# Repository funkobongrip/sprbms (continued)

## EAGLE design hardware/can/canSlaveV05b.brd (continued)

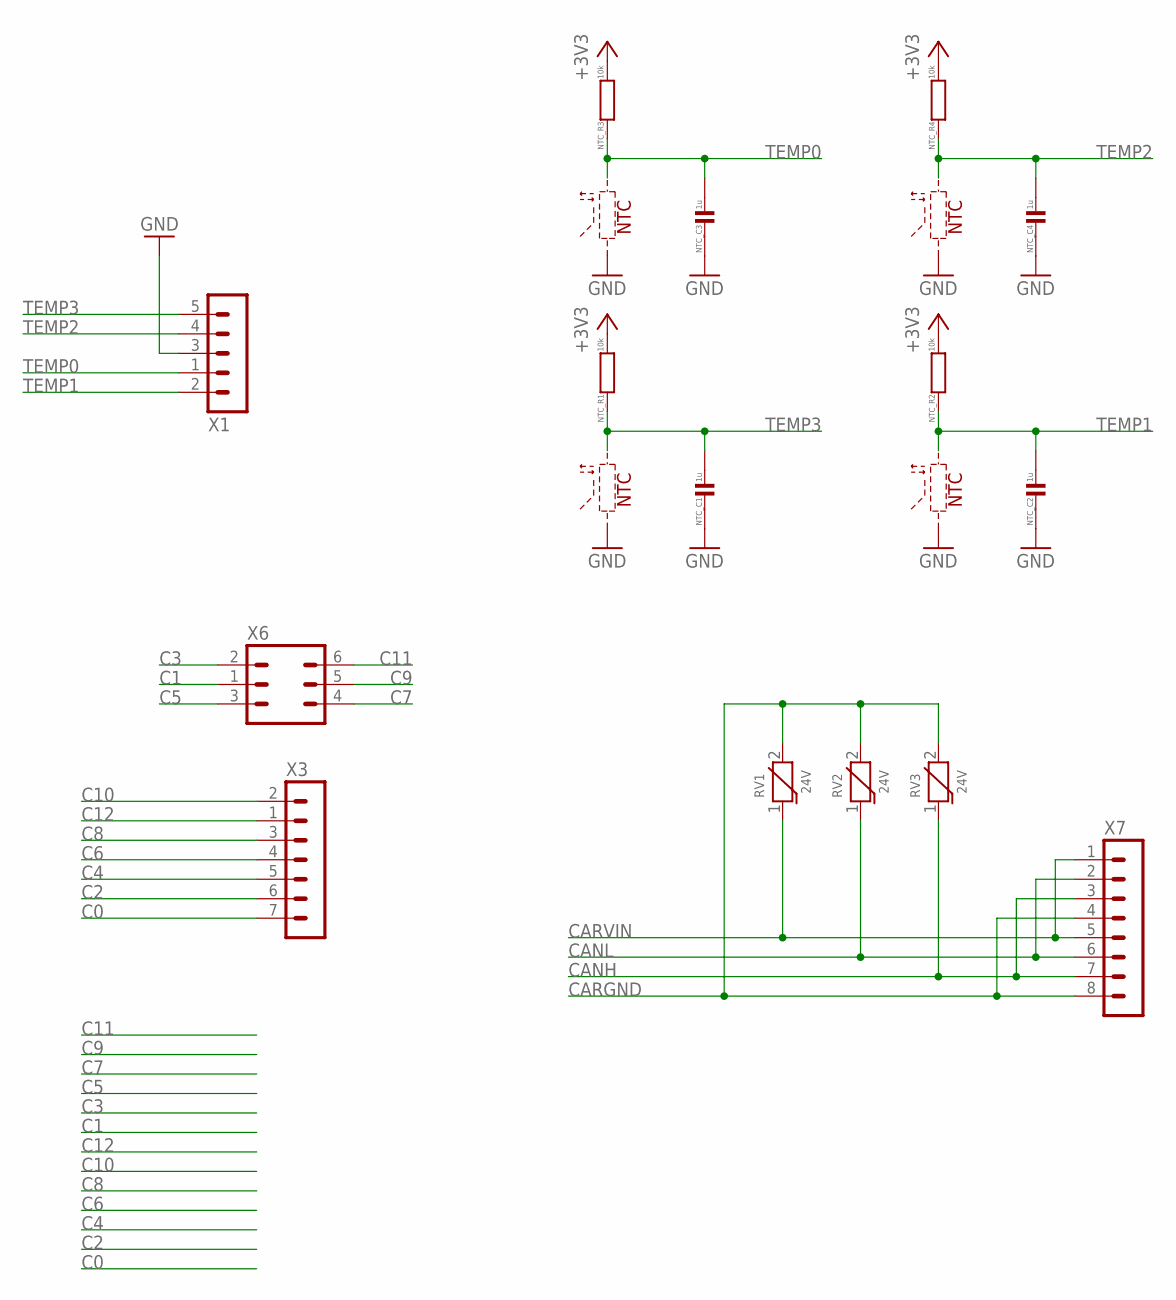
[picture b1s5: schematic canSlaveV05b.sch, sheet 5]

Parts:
NTC_C1, NTC_C2, NTC_C3, NTC_C4: 1u; C0402
NTC_R1, NTC_R2, NTC_R3, NTC_R4: 10k; R0402
RV1: 24V; R0805
RV2, RV3: 24V; R0603
X1: HEADER_POS5_43650-0509; 43650-0509
X3: HEADER_POS7_43650-0709; 43650-0709
X6: HEADER_POS6_43650-0609; 43650-0609
X7: HEADER_POS8_43045-0800; 43045-0800

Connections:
+3V3: NTC_R1.2, NTC_R2.2, NTC_R3.2, NTC_R4.2; also elsewhere on the board
C0: X3.7; also elsewhere on the board
C1: X6.1 (2); also elsewhere on the board
C2: X3.6; also elsewhere on the board
C3: X6.2 (1); also elsewhere on the board
C4: X3.5; also elsewhere on the board
C5: X6.3; also elsewhere on the board
C6: X3.4; also elsewhere on the board
C7: X6.4; also elsewhere on the board
C8: X3.3; also elsewhere on the board
C9: X6.5; also elsewhere on the board
C10: X3.2 (1); also elsewhere on the board
C11: X6.6; also elsewhere on the board
C12: X3.1 (2); also elsewhere on the board
CANH: RV3.1, X7.3, X7.7; also elsewhere on the board
CANL: RV2.1, X7.2, X7.6; also elsewhere on the board
CARGND: RV1.2, RV2.2, RV3.2, X7.4, X7.8; also elsewhere on the board
CARVIN: RV1.1, X7.1, X7.5; also elsewhere on the board
GND: NTC_C1.2, NTC_C2.2, NTC_C3.2, NTC_C4.2, X1.3; also elsewhere on the board
TEMP0: NTC_C3.1, NTC_R3.1, X1.1 (2); also elsewhere on the board
TEMP1: NTC_C2.1, NTC_R2.1, X1.2 (1); also elsewhere on the board
TEMP2: NTC_C4.1, NTC_R4.1, X1.4; also elsewhere on the board
TEMP3: NTC_C1.1, NTC_R1.1, X1.5; also elsewhere on the board

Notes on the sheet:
NTC

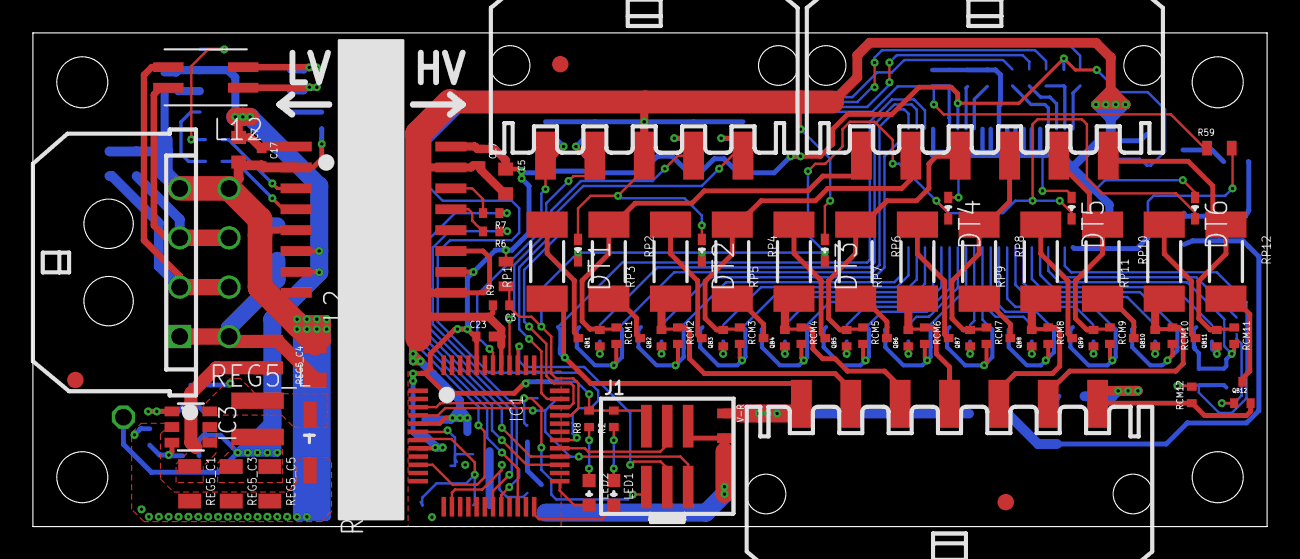
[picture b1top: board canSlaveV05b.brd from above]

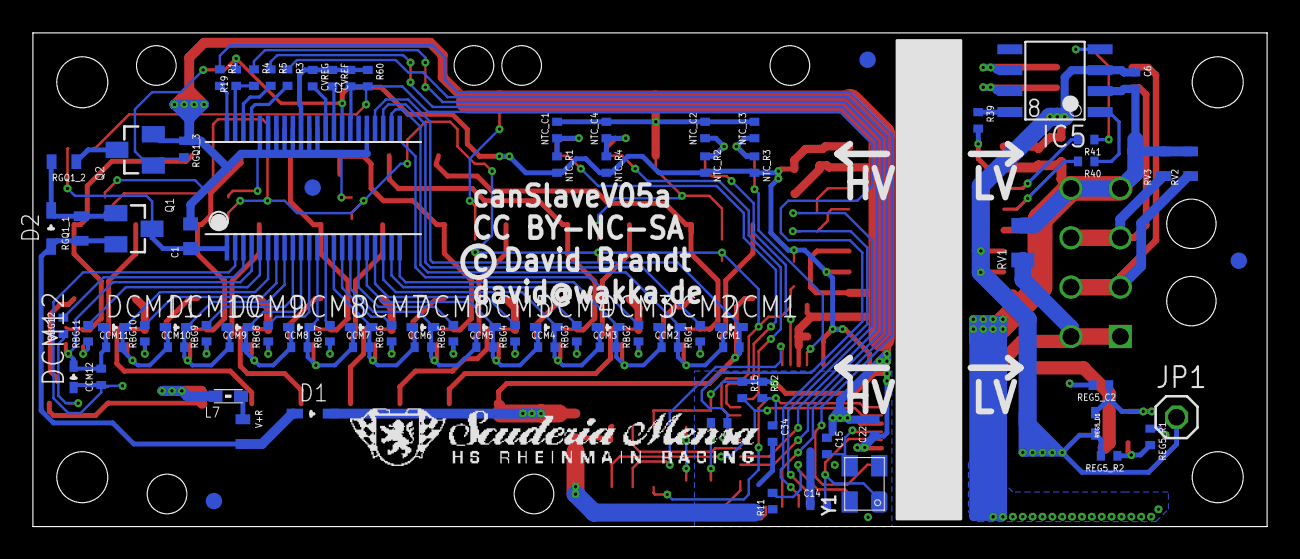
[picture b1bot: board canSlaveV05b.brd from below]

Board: 2 copper layers, 75.0 x 30.0 mm, 167 parts (90 on the bottom side), 115 nets.

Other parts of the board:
U$3: SMLOGOS_BSILK

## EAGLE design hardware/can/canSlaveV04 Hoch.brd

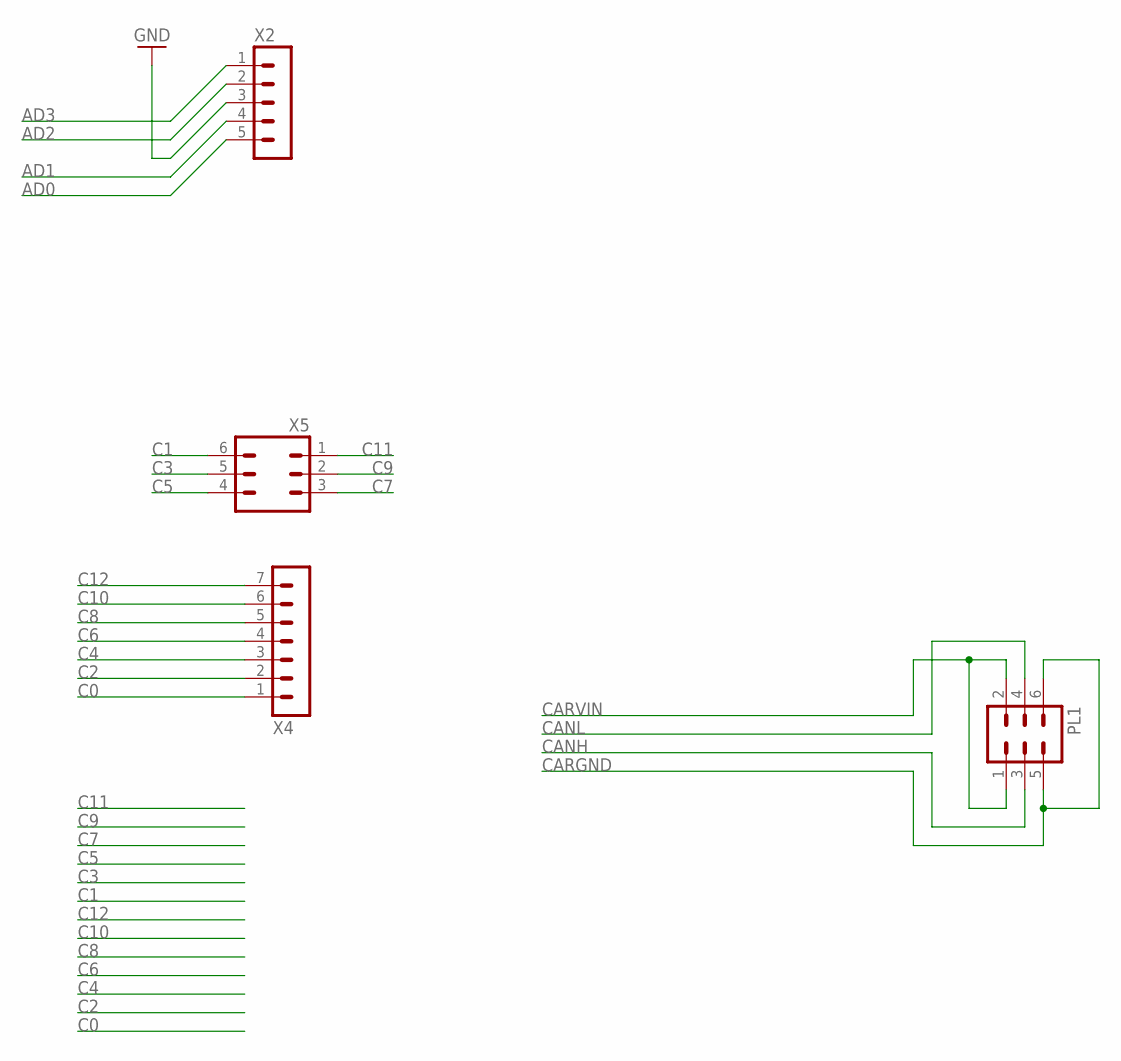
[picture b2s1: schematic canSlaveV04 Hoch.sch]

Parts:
PL1: 06V
X2: HEADER_POS5_43650-0515; 43650-0515
X4: HEADER_POS7_43650-0715; 43650-0715
X5: HEADER_POS6_43650-0615; 43650-0615

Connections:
AD0: X2.5
AD1: X2.4
AD2: X2.2
AD3: X2.1
C0: X4.1
C1: X5.6
C2: X4.2
C3: X5.5
C4: X4.3
C5: X5.4
C6: X4.4
C7: X5.3
C8: X4.5
C9: X5.2
C10: X4.6
C11: X5.1
C12: X4.7
CANH: PL1.3
CANL: PL1.4
CARGND: PL1.5, PL1.6
CARVIN: PL1.1, PL1.2
GND: X2.3

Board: 4 copper layers, 4 parts (0 on the bottom side), 2 nets, no tracks yet.

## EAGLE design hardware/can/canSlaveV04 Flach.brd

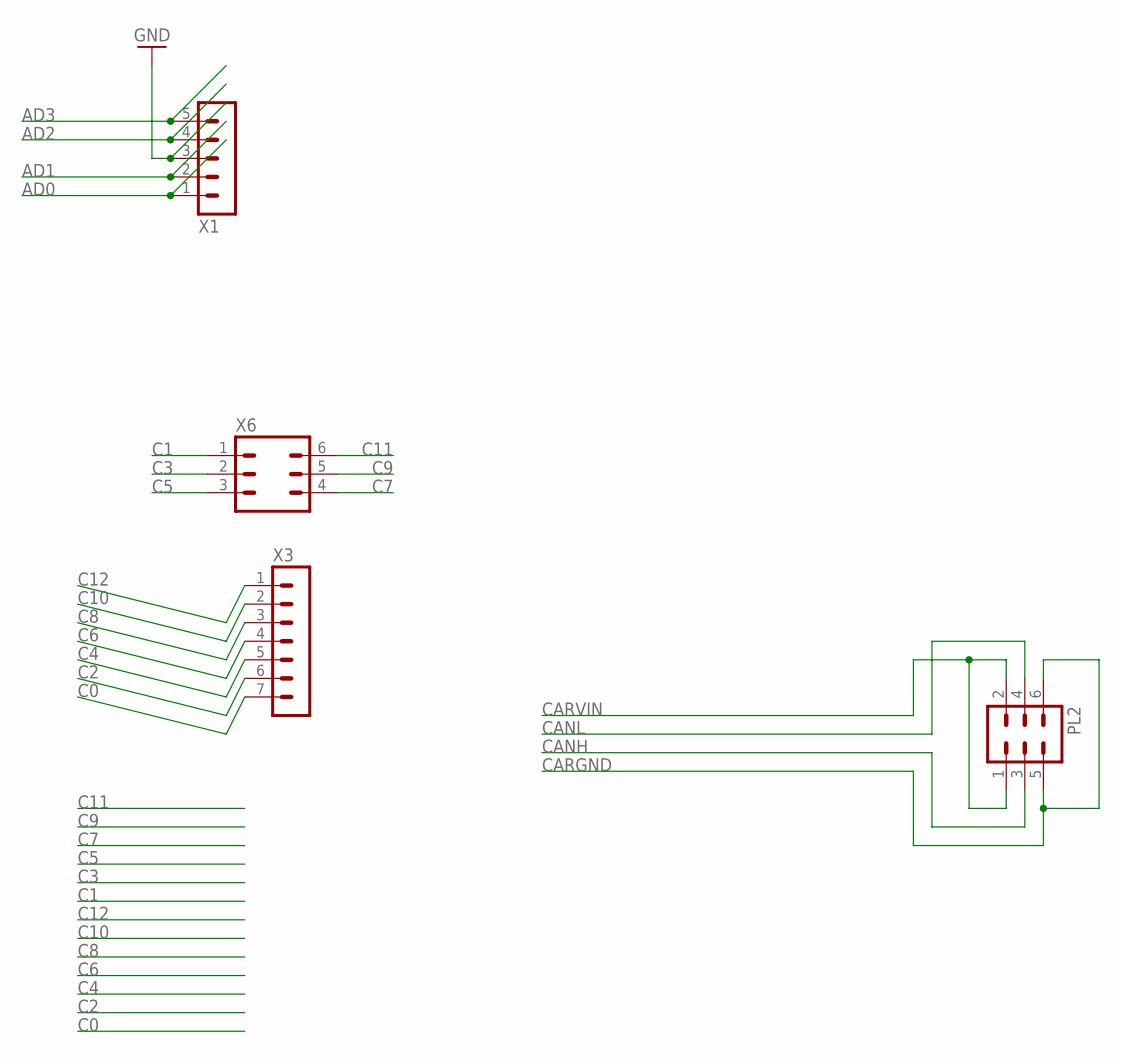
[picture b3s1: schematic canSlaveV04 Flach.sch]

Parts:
PL2: 06H
X1: HEADER_POS5_43650-0500; 43650-0500
X3: HEADER_POS7_43650-0700; 43650-0700
X6: HEADER_POS6_43650-0600; 43650-0600

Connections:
AD0: X1.1
AD1: X1.2
AD2: X1.4
AD3: X1.5
C0: X3.7
C1: X6.1
C2: X3.6
C3: X6.2
C4: X3.5
C5: X6.3
C6: X3.4
C7: X6.4
C8: X3.3
C9: X6.5
C10: X3.2
C11: X6.6
C12: X3.1
CANH: PL2.3
CANL: PL2.4
CARGND: PL2.5, PL2.6
CARVIN: PL2.1, PL2.2
GND: X1.3

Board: 4 copper layers, 4 parts (0 on the bottom side), 2 nets, no tracks yet.

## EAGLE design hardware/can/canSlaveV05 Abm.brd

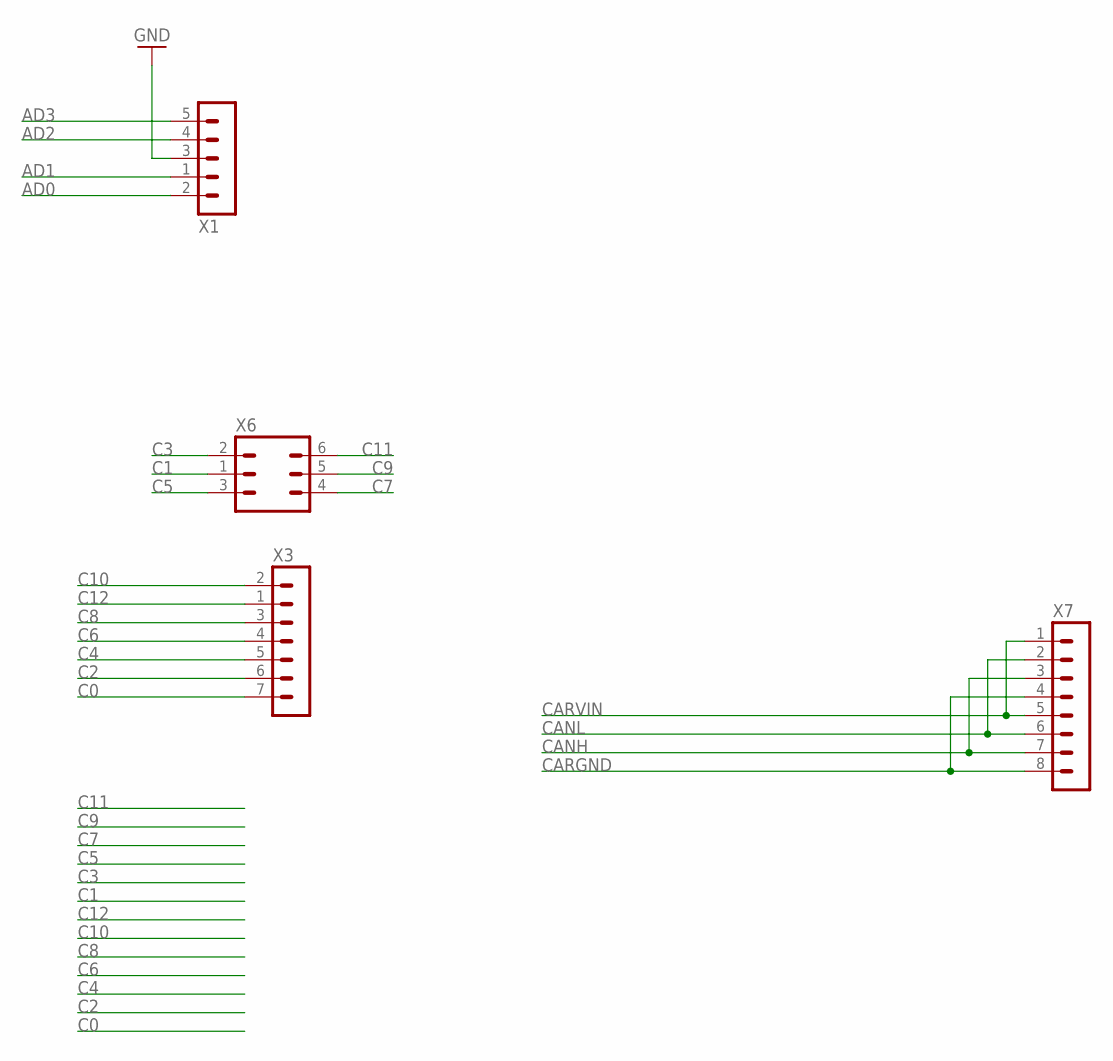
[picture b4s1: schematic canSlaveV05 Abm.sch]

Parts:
X1: HEADER_POS5_43650-0509; 43650-0509
X3: HEADER_POS7_43650-0709; 43650-0709
X6: HEADER_POS6_43650-0609; 43650-0609
X7: HEADER_POS8_43045-0800; 43045-0800

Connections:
AD0: X1.2 (1)
AD1: X1.1 (2)
AD2: X1.4
AD3: X1.5
C0: X3.7
C1: X6.1 (2)
C2: X3.6
C3: X6.2 (1)
C4: X3.5
C5: X6.3
C6: X3.4
C7: X6.4
C8: X3.3
C9: X6.5
C10: X3.2 (1)
C11: X6.6
C12: X3.1 (2)
CANH: X7.3, X7.7
CANL: X7.2, X7.6
CARGND: X7.4, X7.8
CARVIN: X7.1, X7.5
GND: X1.3

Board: 4 copper layers, 4 parts (0 on the bottom side), 4 nets, no tracks yet.

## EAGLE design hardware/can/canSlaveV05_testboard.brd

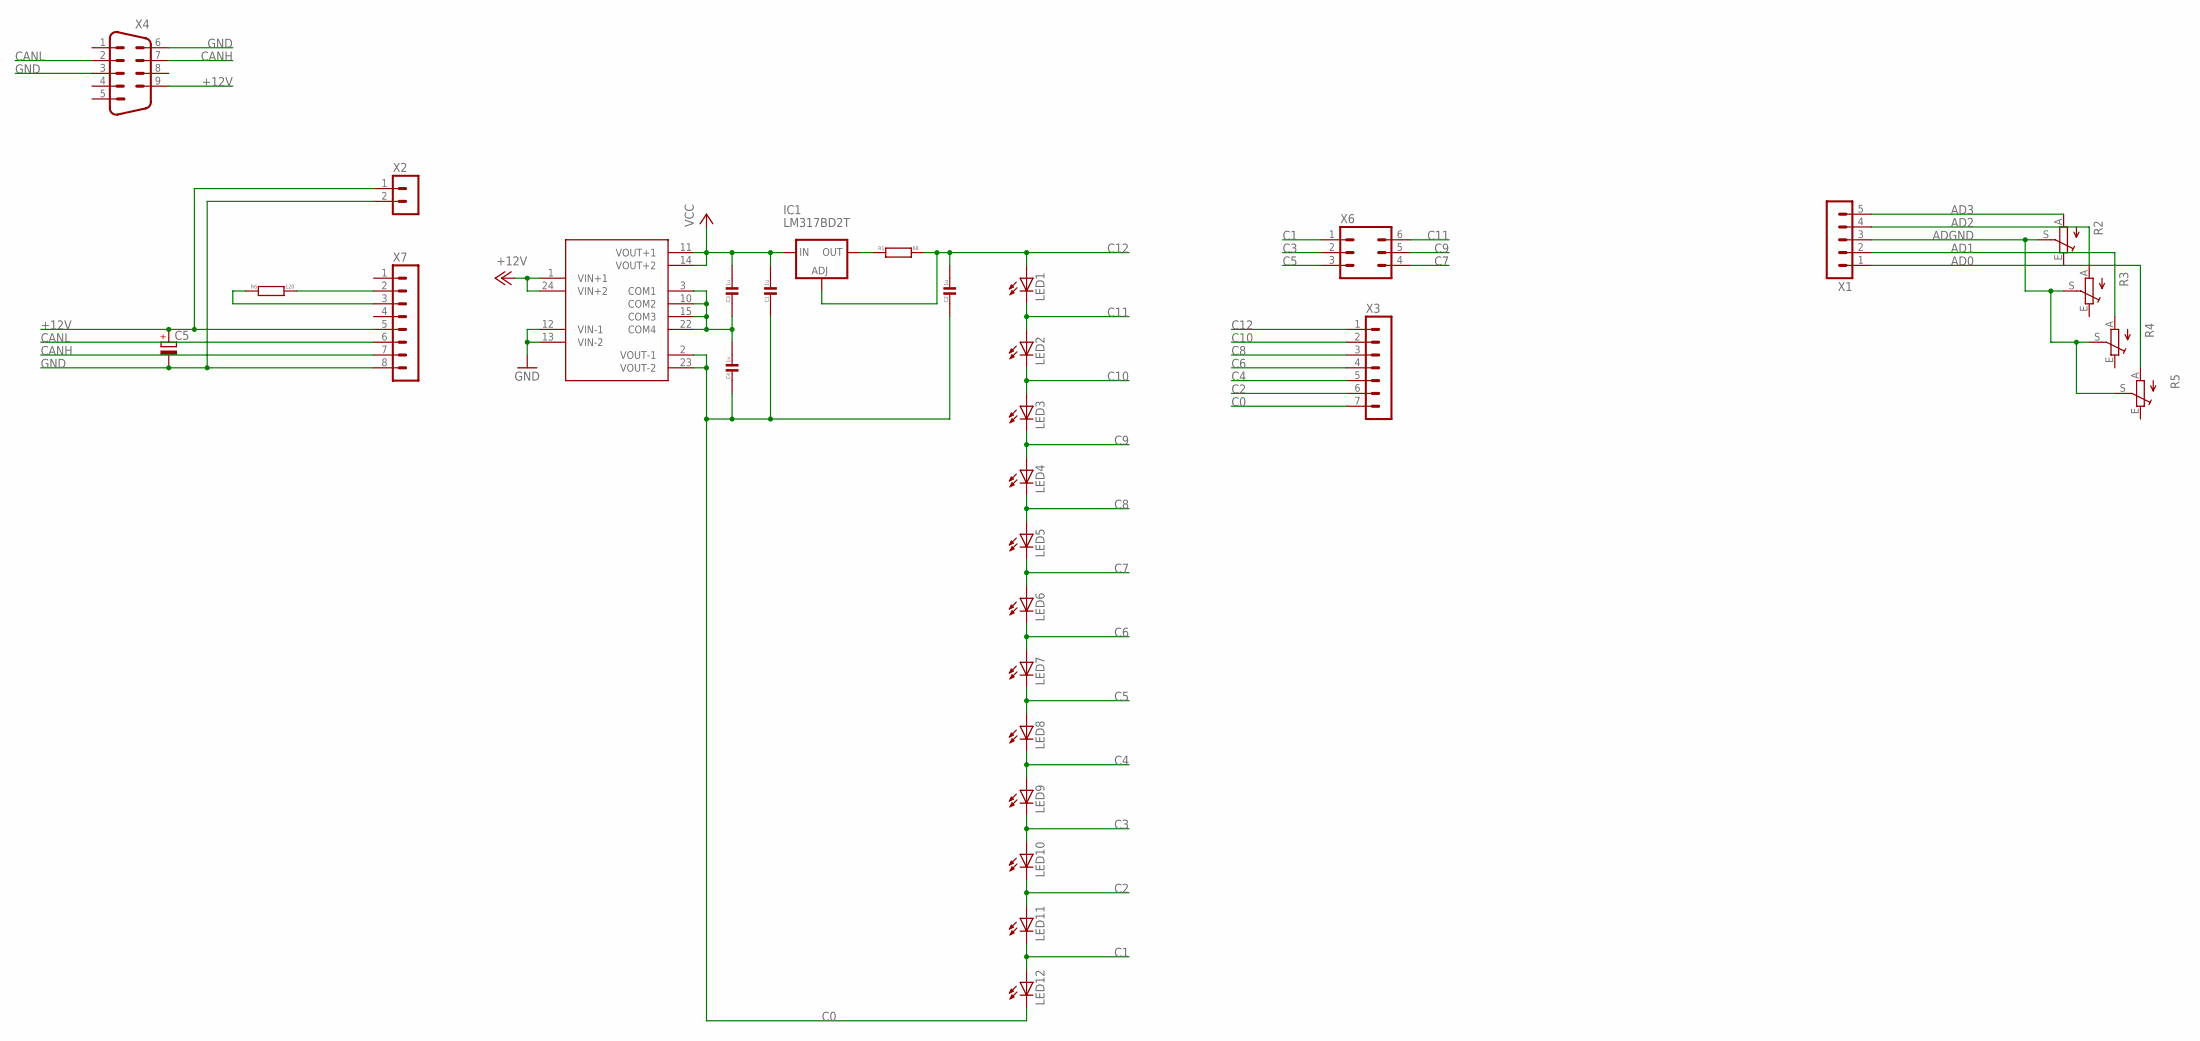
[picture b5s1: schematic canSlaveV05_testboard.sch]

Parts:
C1, C2, C3, C4: 1u; C1206
C5: CPOL-EUE10-20; EB20D
IC1: LM317BD2T; D2PACK
LED1, LED2, LED3, LED4, LED5, LED6, LED7, LED8, LED9, LED10, LED11, LED12: LEDSMT1206; 1206
R1: 68; R1206
R2, R3, R4, R5: TRIM_EU-CIP20C-6MM; CIP20C-6MM
R6: 120; R1206
U$1: JCB0312D24; JCB03
X1: HEADER_POS5_43650-0515; 43650-0515
X2: HEADER_POS2_43650-0215; 43650-0215
X3: HEADER_POS7_43650-0715; 43650-0715
X4: M09HP
X6: HEADER_POS6_43650-0615; 43650-0615
X7: HEADER_POS8_43045-0812; 43045-0812

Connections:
+12V: C5.+, U$1.1 (VIN+1), U$1.24 (VIN+2), X2.1, X4.9, X7.5
AD0: R5.A, X1.1
AD1: R4.A, X1.2
AD2: R3.A, X1.4
AD3: R2.A, X1.5
ADGND: R2.S, R3.S, R4.S, R5.S, X1.3
C0: C1.2, C2.2, C4.2, LED12.C, U$1.2 (VOUT-1), U$1.23 (VOUT-2), X3.7
C1: LED11.C, LED12.A, X6.1
C2: LED10.C, LED11.A, X3.6
C3: LED9.C, LED10.A, X6.2
C4: LED8.C, LED9.A, X3.5
C5: LED7.C, LED8.A, X6.3
C6: LED6.C, LED7.A, X3.4
C7: LED5.C, LED6.A, X6.4
C8: LED4.C, LED5.A, X3.3
C9: LED3.C, LED4.A, X6.5
C10: LED2.C, LED3.A, X3.2
C11: LED1.C, LED2.A, X6.6
C12: C2.1, IC1.1 (ADJ), LED1.A, R1.2, X3.1
CANH: X4.7, X7.7
CANL: X4.2, X7.6
CANR1: R6.1, X7.3
CANR2: R6.2, X7.2
COMM: C3.2, C4.1, U$1.3 (COM1), U$1.10 (COM2), U$1.15 (COM3), U$1.22 (COM4)
GND: C5.-, U$1.12 (VIN-1), U$1.13 (VIN-2), X2.2, X4.3, X4.6, X7.8
LM317O: IC1.2 (OUT), R1.1
VCC: C1.1, C3.1, IC1.3 (IN), U$1.11 (VOUT+1), U$1.14 (VOUT+2)

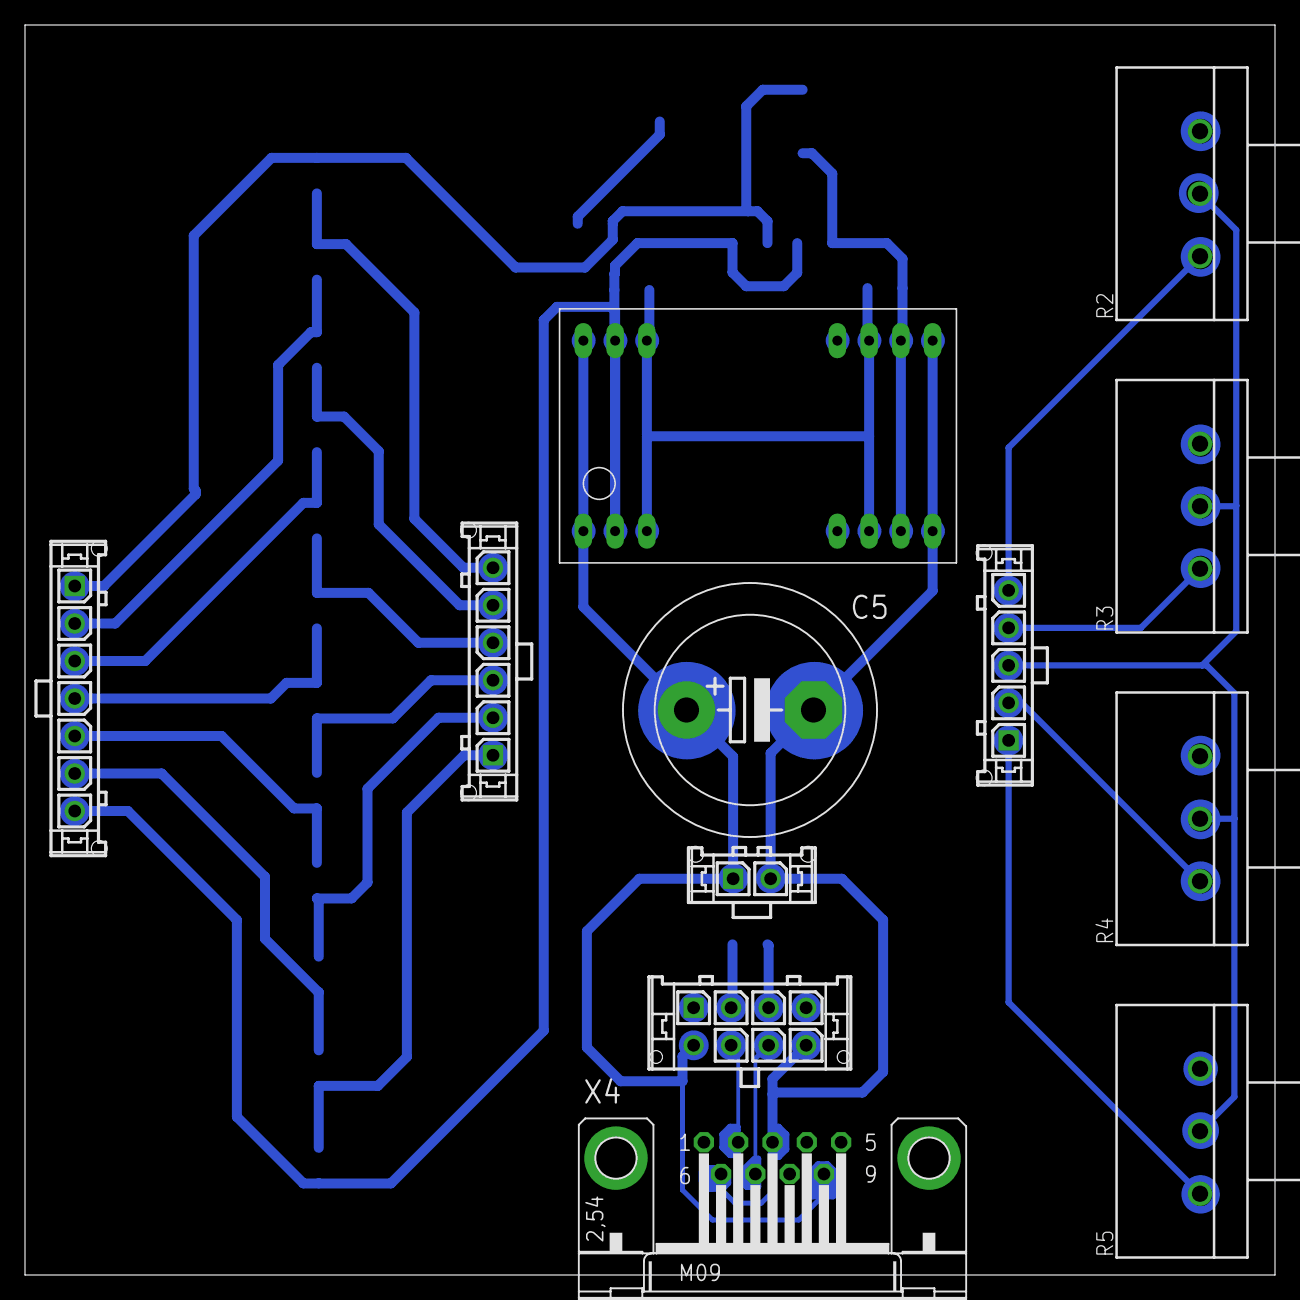
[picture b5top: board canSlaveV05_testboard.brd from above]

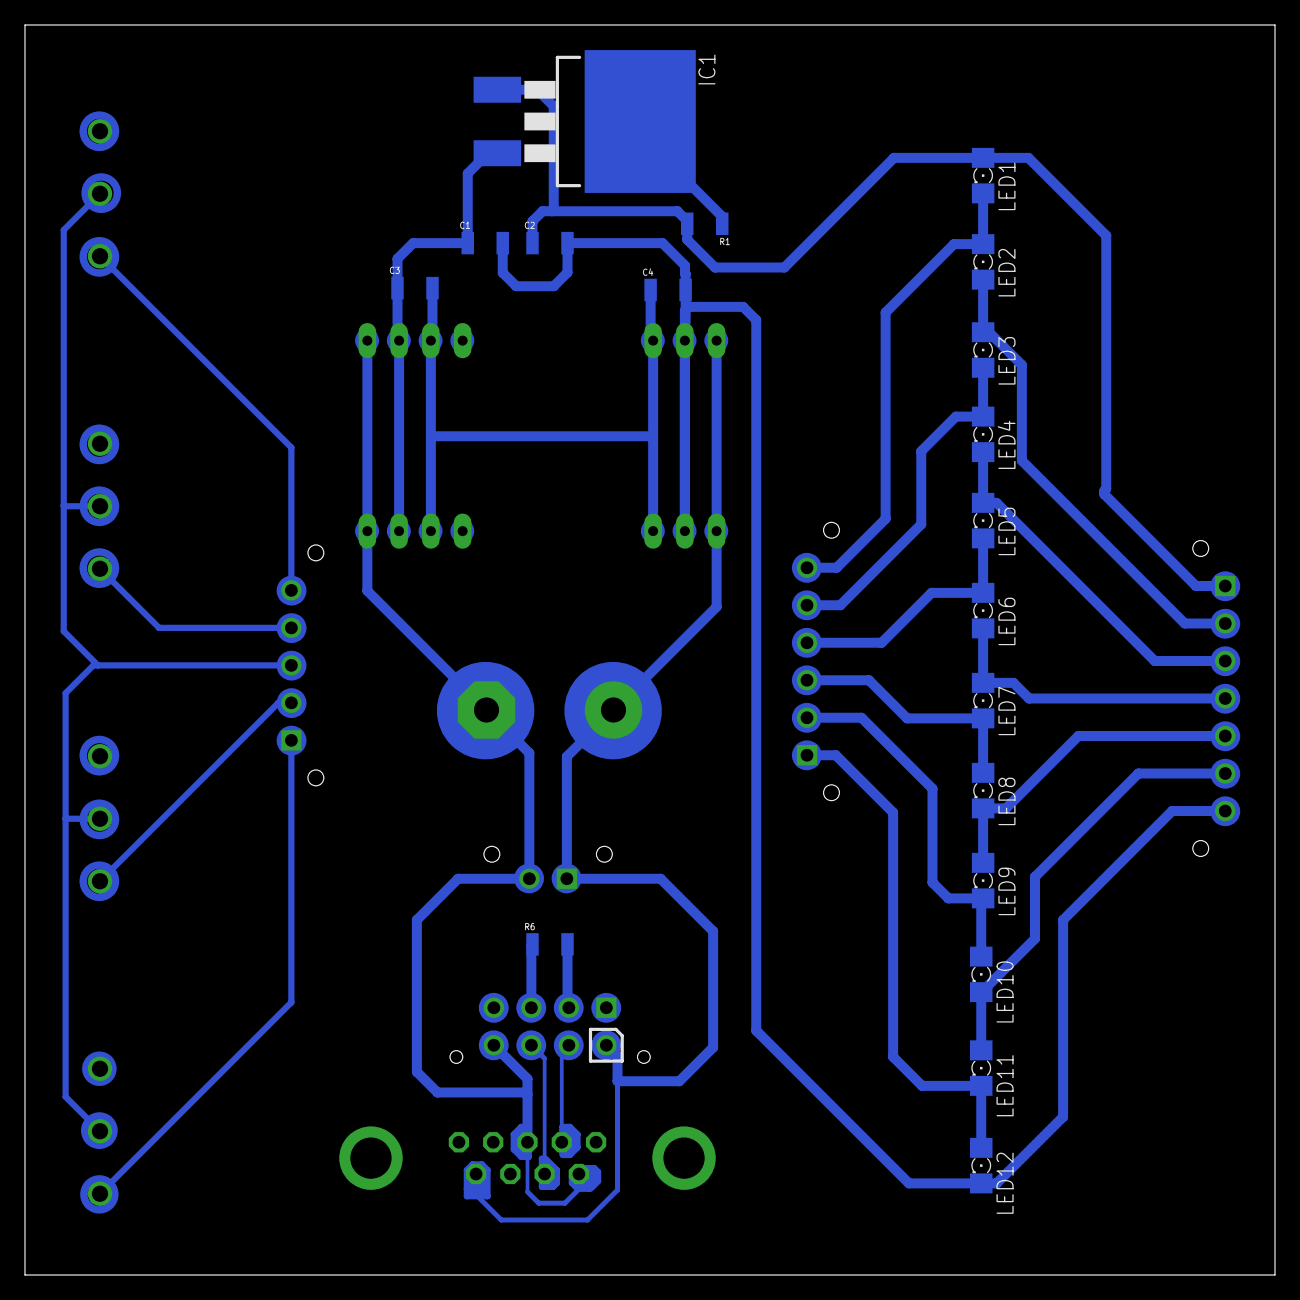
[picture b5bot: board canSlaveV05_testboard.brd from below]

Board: 2 copper layers, 100.0 x 100.0 mm, 31 parts (19 on the bottom side), 27 nets.

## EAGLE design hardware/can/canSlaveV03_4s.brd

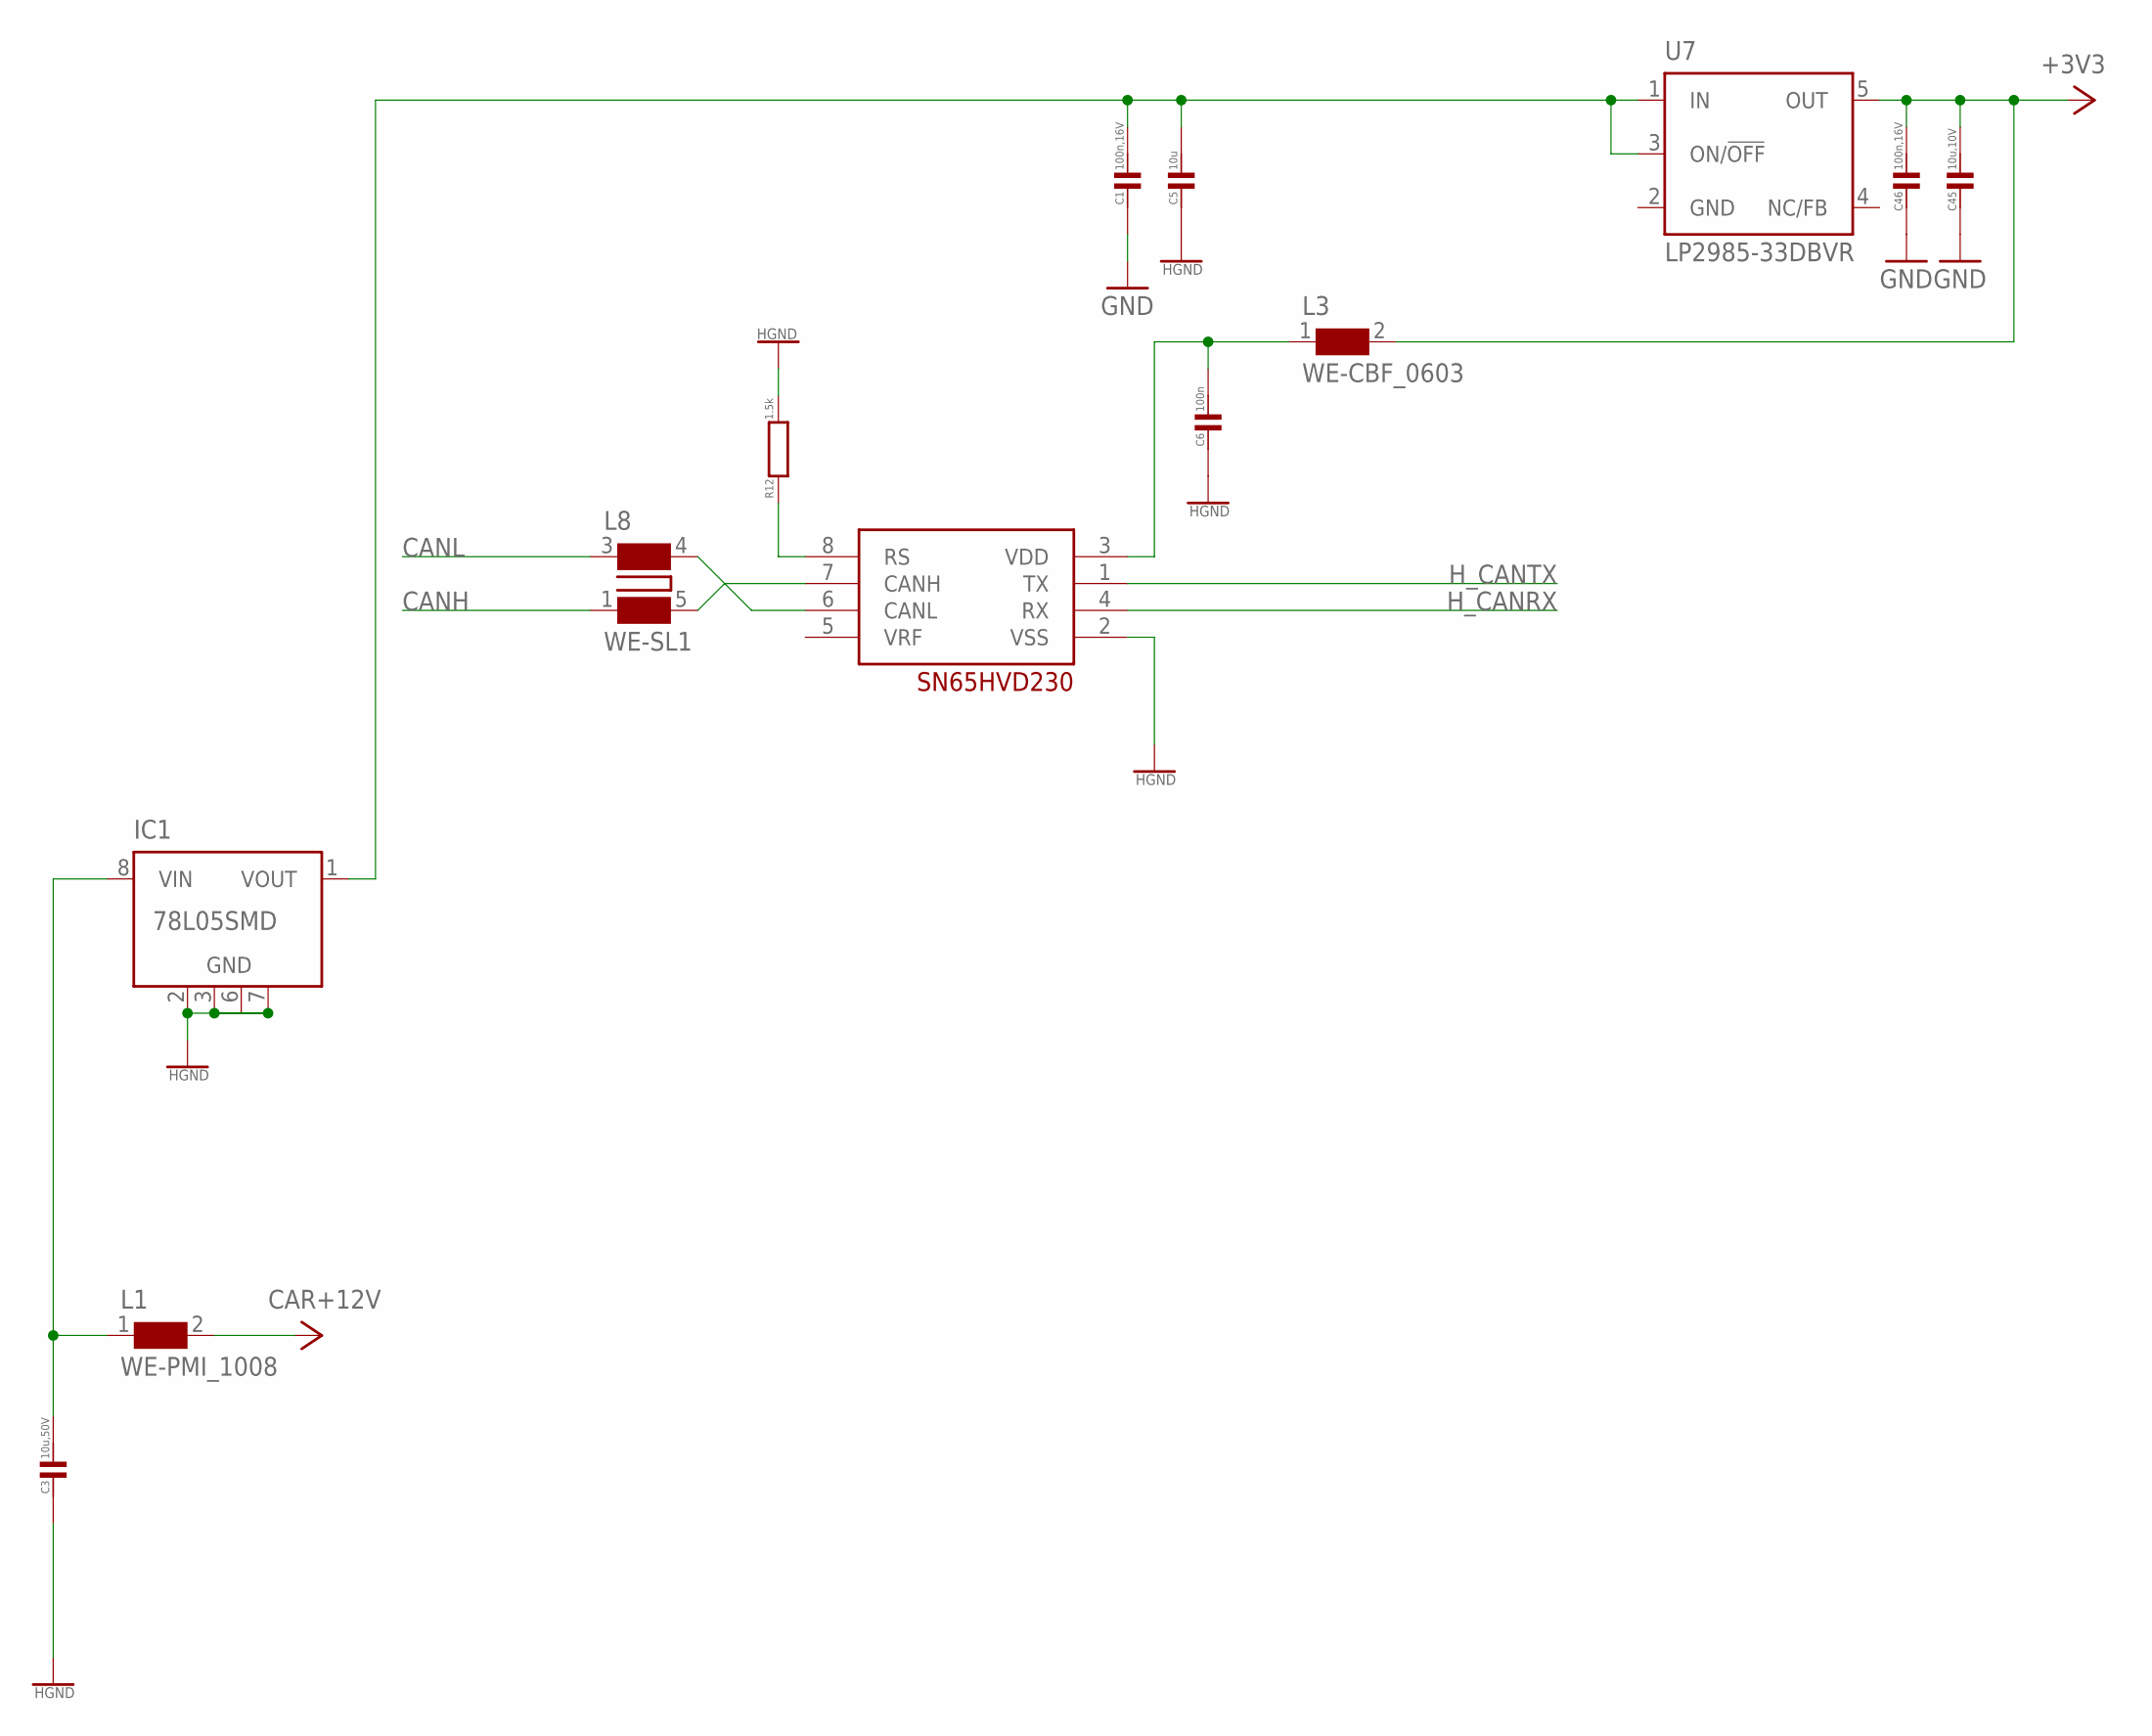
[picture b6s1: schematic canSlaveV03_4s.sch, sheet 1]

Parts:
C1, C46: 100n,16V; C0603
C3: 10u,50V; C1206
C5: 10u; C0603
C6: 100n; C0603
C45: 10u,10V; C0603
IC1: 78L05SMD; SO08
IC4: SN65HVD230; SO-8
L1: WE-PMI_1008
L3: WE-CBF_0603; 0603
L8: WE-SL1
R12: 1.5k; R0603
U7: LP2985-33DBVR; SOT23-DBV

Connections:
CANH: L8.1; also elsewhere on the board
CANL: L8.3; also elsewhere on the board
CAR+5V: C1.1, C5.1, IC1.1 (VOUT), U7.1 (IN), U7.3 (ON/!OFF)
CAR+5V_H: C6.1, IC4.3 (VDD), L3.1
CAR+12V: L1.2; also elsewhere on the board
CAR+12VFILT: C3.1, IC1.8 (VIN), L1.1
H+3V3: C45.1, C46.1, L3.2, U7.5 (OUT); also elsewhere on the board
HCANHL: IC4.7 (CANH), L8.5 (2)
HCANLL: IC4.6 (CANL), L8.4
HGND: C1.2, C3.2, C5.2, C6.2, C45.2, C46.2, IC1.2 (GND), IC1.3 (GND), IC1.6 (GND), IC1.7 (GND), IC4.2 (VSS), R12.2, U7.2 (GND); also elsewhere on the board
H_CANRX: IC4.4 (RX); also elsewhere on the board
H_CANTX: IC4.1 (TX); also elsewhere on the board
RS: IC4.8 (RS), R12.1
